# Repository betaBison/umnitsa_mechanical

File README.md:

# umnitsa_mechanical

This package contains the necessary files to turn the design of the umnitsa robot into reality.

Umnitsa comes from the englsih transliteration of the russian word "умница" clever pesron or smarty-pants. Umnitsa is designed to be a clever robot.

See also [umnitsa_msgs](https://github.com/betaBison/umnitsa_msgs), [umnitsa_robot](https://github.com/betaBison/umnitsa_robot), and [umnitsa_gs](https://github.com/betaBison/umnitsa_gs).

<p align="center">
  <em>design into reality</em>
 </p>
   
`/PCBDesigns` contains all the custom PCB designs that are used on the robot and includes it's own README.  

`/logos` contains umnitsa logos  

`/Drawings` contains all the .DXF files that are created from the OnShape models of [Umnitsa Pi](www.google.com) or [Umnitsa Nano](www.google.com).

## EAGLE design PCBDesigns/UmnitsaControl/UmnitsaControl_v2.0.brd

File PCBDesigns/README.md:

# Umnitsa Custom PCB Designs
Each folder contains the Eagle PCB schematic and board layout as well as the gerber files.

## UmnitsaControl
UmnitsaControl is the PCB for the motor control of four DC 12 V motors using two
Pololu-A4990 Motor Driver Carriers. Rated for 1.0 Amp for each motor and 2.5 Amp total.  
**Inputs:** 12 V supply, RasPi 10 control inputs  
**Outputs:** 12 V pins, 4 Motor Outputs, A4990 error pins (optional)  

")

## UmnitsaRGB
UmnitsaRGB is used to control 8 RGB LEDs with only 3 pin inputs from the RasPi by using
three HC595 shift registers.  
**Inputs:** 5 V supply, RasPi 3 control inputs  
**Outputs:** 5 V pins, 8 RGB LED Outputs  

## UmnitsaUltrasonic
UmnitsaRGB is used to receive data from four HC-SR04 ultrasonic sensors.  

**Inputs:** 5 V supply, RasPi control inputs  
**Outputs:** 5 V pins, 4 HC-SR04 inputs/outputs

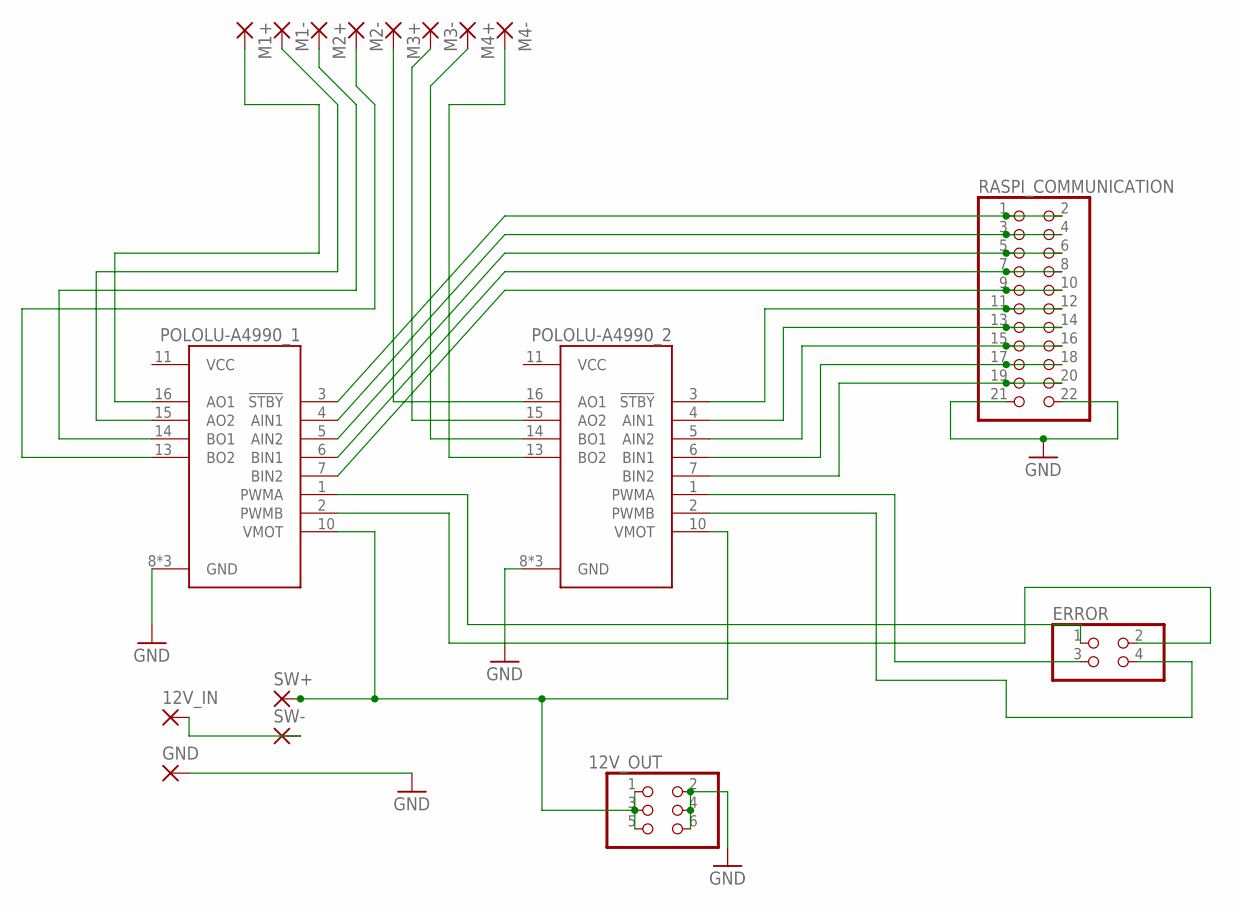
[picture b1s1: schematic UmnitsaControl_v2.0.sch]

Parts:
12V_IN: 3,81/1,4
12V_OUT: PINHD-2X3; 2X03
ERROR: PINHD-2X2; 2X02
GND: 3,81/1,4
M1+, M1-, M2+, M2-, M3+, M3-, M4+, M4-: 3,81/1,4
POLOLU-A4990_1, POLOLU-A4990_2: POLOLU-713; SHIELD_POLOLU-713
RASPI_COMMUNICATION: PINHD-2X11; 2X11
SW+: 2,54/1,0
SW-: 2,54/1,0

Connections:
GND: 12V_OUT.2, 12V_OUT.4, 12V_OUT.6, GND.1, POLOLU-A4990_1.8 (GND), POLOLU-A4990_1.9 (GND), POLOLU-A4990_1.12 (GND), POLOLU-A4990_2.8 (GND), POLOLU-A4990_2.9 (GND), POLOLU-A4990_2.12 (GND), RASPI_COMMUNICATION.21, RASPI_COMMUNICATION.22
unnamed: M1+.1, POLOLU-A4990_1.16 (AO1)
unnamed: M1-.1, POLOLU-A4990_1.15 (AO2)
unnamed: 12V_IN.1, SW-.1
unnamed: M2+.1, POLOLU-A4990_1.14 (BO1)
unnamed: M2-.1, POLOLU-A4990_1.13 (BO2)
unnamed: M3+.1, POLOLU-A4990_2.16 (AO1)
unnamed: M3-.1, POLOLU-A4990_2.15 (AO2)
unnamed: M4+.1, POLOLU-A4990_2.14 (BO1)
unnamed: M4-.1, POLOLU-A4990_2.13 (BO2)
unnamed: POLOLU-A4990_2.3 (!STBY), RASPI_COMMUNICATION.11, RASPI_COMMUNICATION.12
unnamed: POLOLU-A4990_2.7 (BIN2), RASPI_COMMUNICATION.19, RASPI_COMMUNICATION.20
unnamed: POLOLU-A4990_2.6 (BIN1), RASPI_COMMUNICATION.17, RASPI_COMMUNICATION.18
unnamed: POLOLU-A4990_2.5 (AIN2), RASPI_COMMUNICATION.15, RASPI_COMMUNICATION.16
unnamed: POLOLU-A4990_2.4 (AIN1), RASPI_COMMUNICATION.13, RASPI_COMMUNICATION.14
unnamed: POLOLU-A4990_1.3 (!STBY), RASPI_COMMUNICATION.1, RASPI_COMMUNICATION.2
unnamed: POLOLU-A4990_1.4 (AIN1), RASPI_COMMUNICATION.3, RASPI_COMMUNICATION.4
unnamed: POLOLU-A4990_1.5 (AIN2), RASPI_COMMUNICATION.5, RASPI_COMMUNICATION.6
unnamed: POLOLU-A4990_1.6 (BIN1), RASPI_COMMUNICATION.7, RASPI_COMMUNICATION.8
unnamed: POLOLU-A4990_1.7 (BIN2), RASPI_COMMUNICATION.9, RASPI_COMMUNICATION.10
unnamed: ERROR.3, POLOLU-A4990_2.1 (PWMA)
unnamed: ERROR.4, POLOLU-A4990_2.2 (PWMB)
unnamed: ERROR.1, POLOLU-A4990_1.1 (PWMA)
unnamed: ERROR.2, POLOLU-A4990_1.2 (PWMB)
unnamed: 12V_OUT.1, 12V_OUT.3, 12V_OUT.5, POLOLU-A4990_1.10 (VMOT), POLOLU-A4990_2.10 (VMOT), SW+.1
VCC: POLOLU-A4990_1.11 (VCC), POLOLU-A4990_2.11 (VCC)

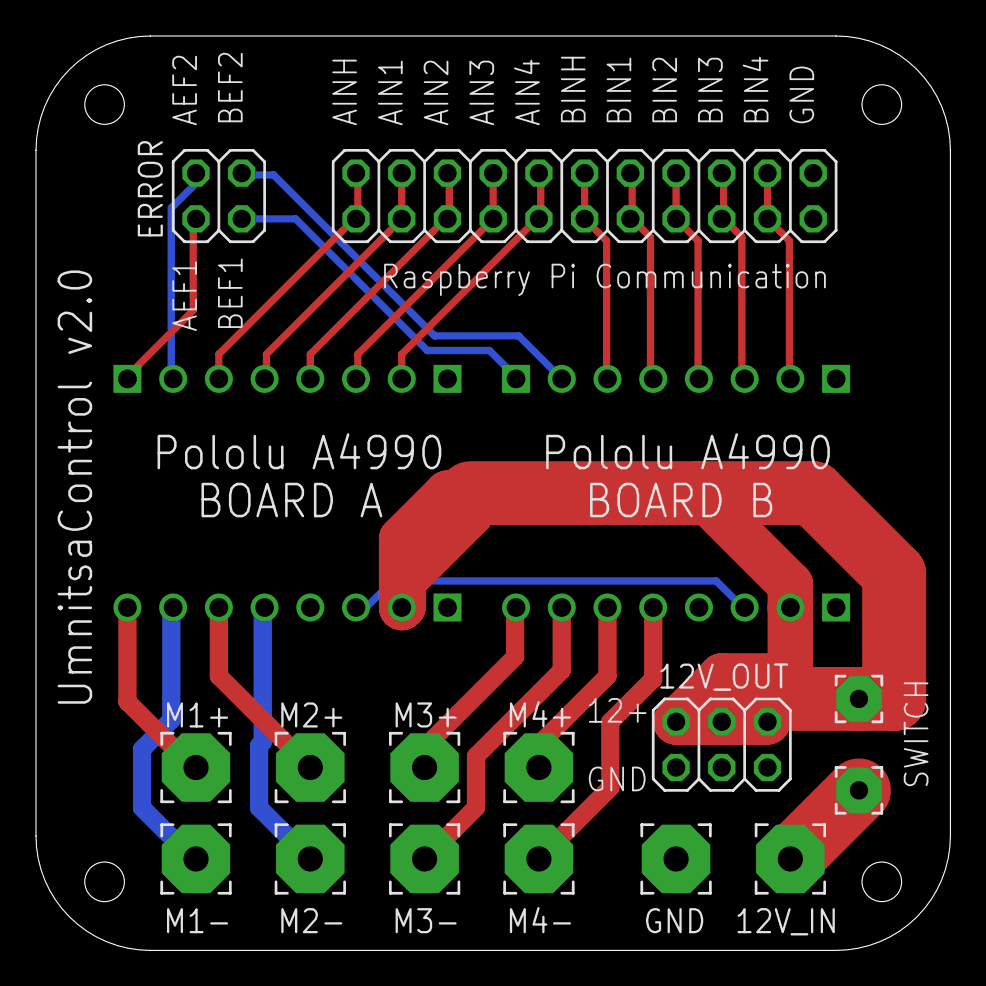
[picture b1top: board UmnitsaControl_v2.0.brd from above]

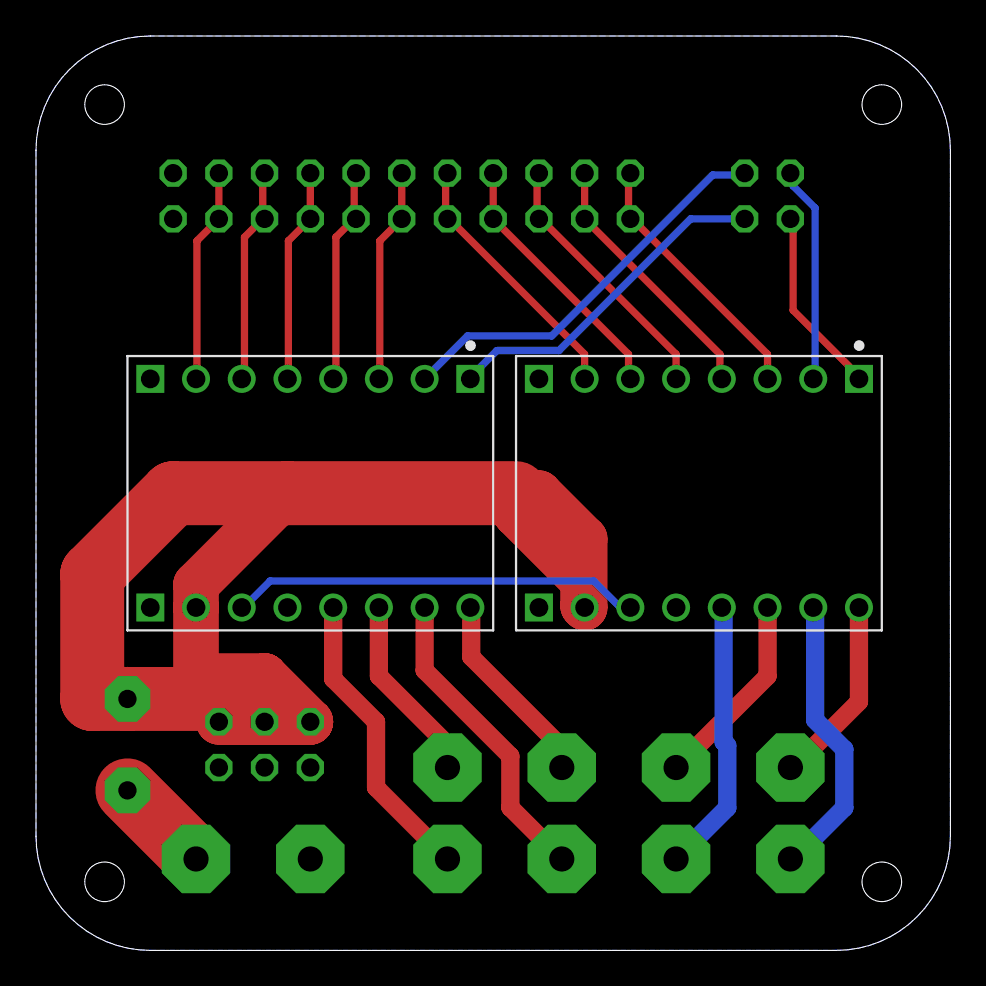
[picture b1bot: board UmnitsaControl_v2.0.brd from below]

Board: 2 copper layers, 50.8 x 50.8 mm, 17 parts (2 on the bottom side), 26 nets.

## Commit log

2019-03-23 PCB Design files
2019-03-23 PCB documentation
2019-03-23 file name error
2019-03-23 file name change
2019-03-23 current rating for UmnitsaControl
2019-05-08 moved PCBDesigns into sub directory
2019-05-13 added logos
2019-05-13 moved logos into folder
2019-05-16 created documentation
2019-05-17 update caption
2019-05-21 update to show other packages
2019-08-13 add license
